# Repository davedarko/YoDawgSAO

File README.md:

# Yo Dawg, I heard you like add-ons on your badges?
With the hackaday supercon add-on contest in 2024, 
there came a lot of self-inflicted pressure of doing something great with the I2C pins and slap something smart on the PCBs. 
This sounded great, but what if you just want to do a small meme or have some RGB LEDs blinking?
What if you feel like that is not worthy of being a simple add-on made for the contest?

## design choices
To be safe with distance between badges, I decided on having the size constrained to 19mm x 19mm and using a 1.27mm pin header to connect GND-VCC-GND to the simple add-on mainboard. 
This header size was the wrong decision as it is a pain to solder - but it's the standard now!

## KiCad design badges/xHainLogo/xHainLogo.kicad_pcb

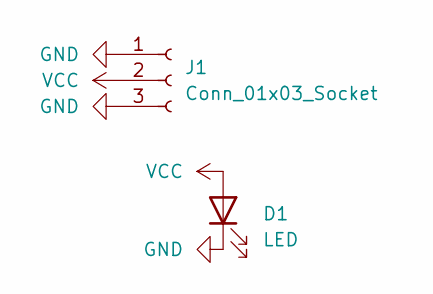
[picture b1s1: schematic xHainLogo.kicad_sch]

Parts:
D1: LED; LED_1210_3225Metric_Pad1.42x2.65mm_HandSolder
J1: Conn_01x03_Socket; PinHeader_1x03_P1.27mm_Vertical

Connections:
GND: D1.1 (K), J1.1, J1.3
VCC: D1.2 (A), J1.2

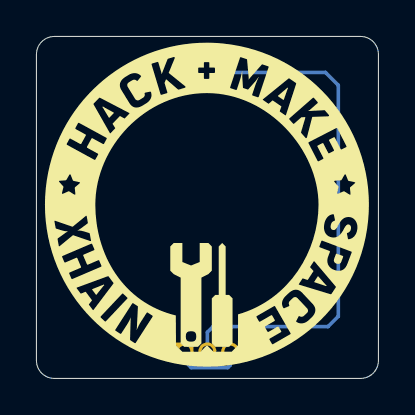
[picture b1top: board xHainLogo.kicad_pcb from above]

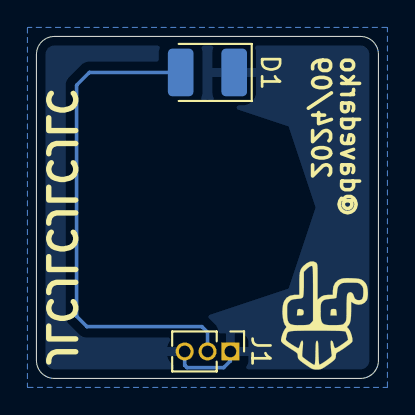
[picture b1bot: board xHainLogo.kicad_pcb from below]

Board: 2 copper layers, 19.0 x 19.0 mm, 3 parts (3 on the bottom side), 2 nets.

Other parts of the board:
Ref**: Val**; davedarko_logo_silk_outline

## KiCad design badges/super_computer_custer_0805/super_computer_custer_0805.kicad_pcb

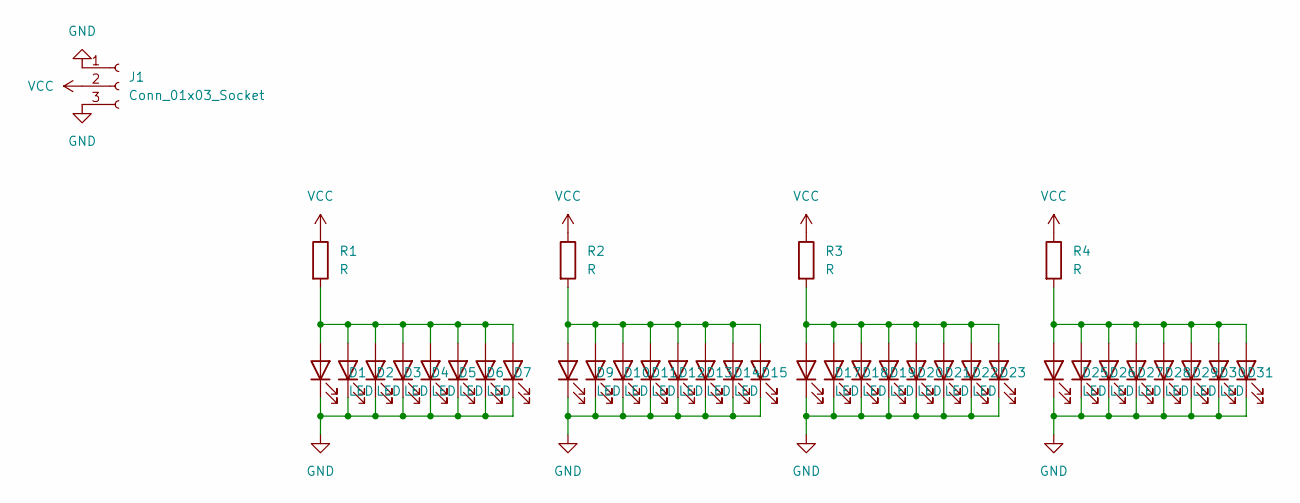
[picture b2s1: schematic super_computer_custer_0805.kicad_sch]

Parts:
D1, D2, D3, D4, D5, D6, D7, D8, D9, D10, D11, D12, D13, D14, D15, D16, D17, D18, D19, D20, D21, D22, D23, D24, D25, D26, D27, D28, D29, D30, D31, D32: LED; LED_0805_2012Metric_Pad1.15x1.40mm_HandSolder
J1: Conn_01x03_Socket; PinHeader_1x03_P1.27mm_Vertical
R1, R2, R3, R4: R; R_0603_1608Metric_Pad0.98x0.95mm_HandSolder

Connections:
GND: D1.1 (K), D2.1 (K), D3.1 (K), D4.1 (K), D5.1 (K), D6.1 (K), D7.1 (K), D8.1 (K), D9.1 (K), D10.1 (K), D11.1 (K), D12.1 (K), D13.1 (K), D14.1 (K), D15.1 (K), D16.1 (K), D17.1 (K), D18.1 (K), D19.1 (K), D20.1 (K), D21.1 (K), D22.1 (K), D23.1 (K), D24.1 (K), D25.1 (K), D26.1 (K), D27.1 (K), D28.1 (K), D29.1 (K), D30.1 (K), D31.1 (K), D32.1 (K), J1.1, J1.3
unnamed: D1.2 (A), D2.2 (A), D3.2 (A), D4.2 (A), D5.2 (A), D6.2 (A), D7.2 (A), D8.2 (A), R1.2
unnamed: D9.2 (A), D10.2 (A), D11.2 (A), D12.2 (A), D13.2 (A), D14.2 (A), D15.2 (A), D16.2 (A), R2.2
unnamed: D17.2 (A), D18.2 (A), D19.2 (A), D20.2 (A), D21.2 (A), D22.2 (A), D23.2 (A), D24.2 (A), R3.2
unnamed: D25.2 (A), D26.2 (A), D27.2 (A), D28.2 (A), D29.2 (A), D30.2 (A), D31.2 (A), D32.2 (A), R4.2
VCC: J1.2, R1.1, R2.1, R3.1, R4.1

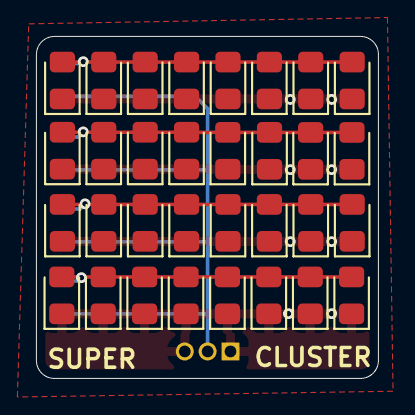
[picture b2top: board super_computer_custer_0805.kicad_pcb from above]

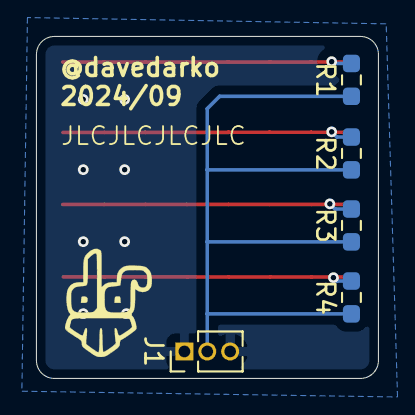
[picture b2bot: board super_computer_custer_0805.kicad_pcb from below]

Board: 2 copper layers, 19.0 x 19.0 mm, 38 parts (6 on the bottom side), 6 nets.

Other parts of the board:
Ref**: Val**; davedarko_logo_silk_outline

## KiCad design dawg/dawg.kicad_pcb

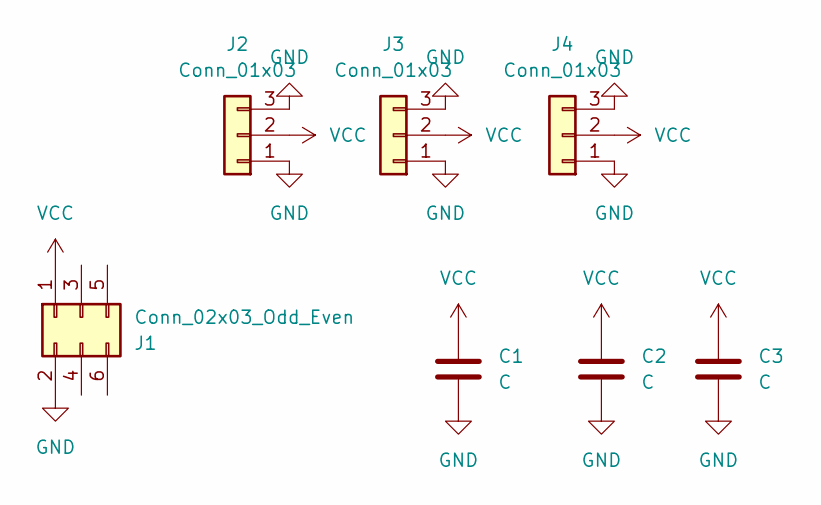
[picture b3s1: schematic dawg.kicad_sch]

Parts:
C1, C2, C3: C; C_0805_2012Metric_Pad1.18x1.45mm_HandSolder
J1: Conn_02x03_Odd_Even; IDC-Header_2x03_P2.54mm_Vertical
J2, J3, J4: Conn_01x03; PinSocket_1x03_P1.27mm_Vertical

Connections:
GND: C1.2, C2.2, C3.2, J1.2, J2.1, J2.3, J3.1, J3.3, J4.1, J4.3
VCC: C1.1, C2.1, C3.1, J1.1, J2.2, J3.2, J4.2

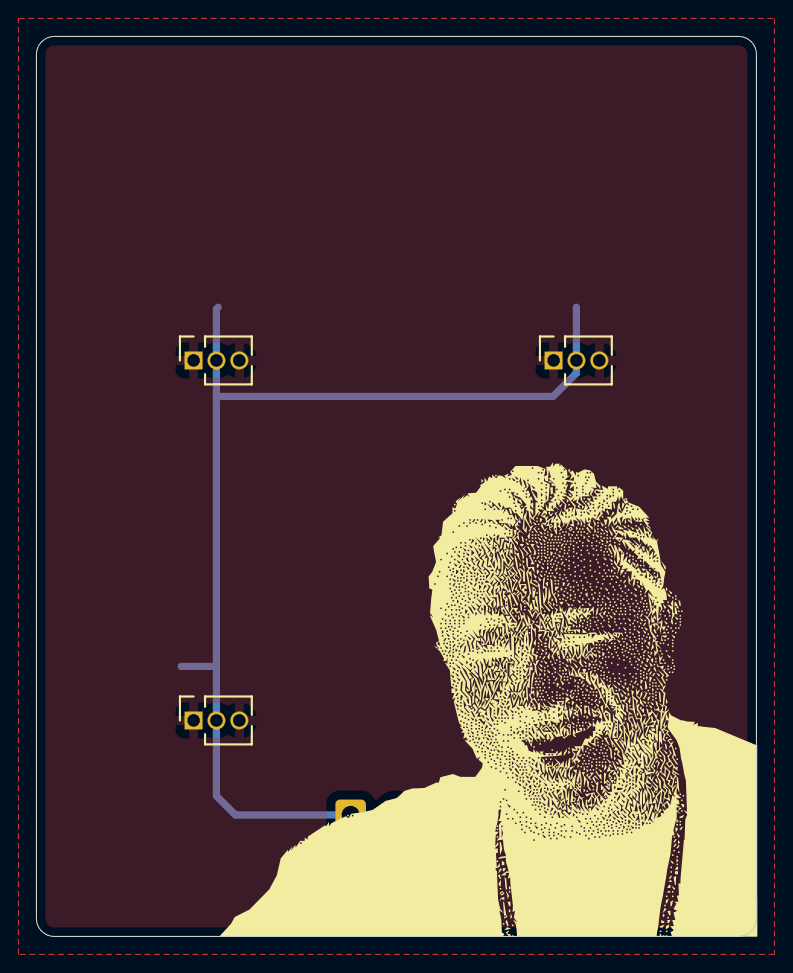
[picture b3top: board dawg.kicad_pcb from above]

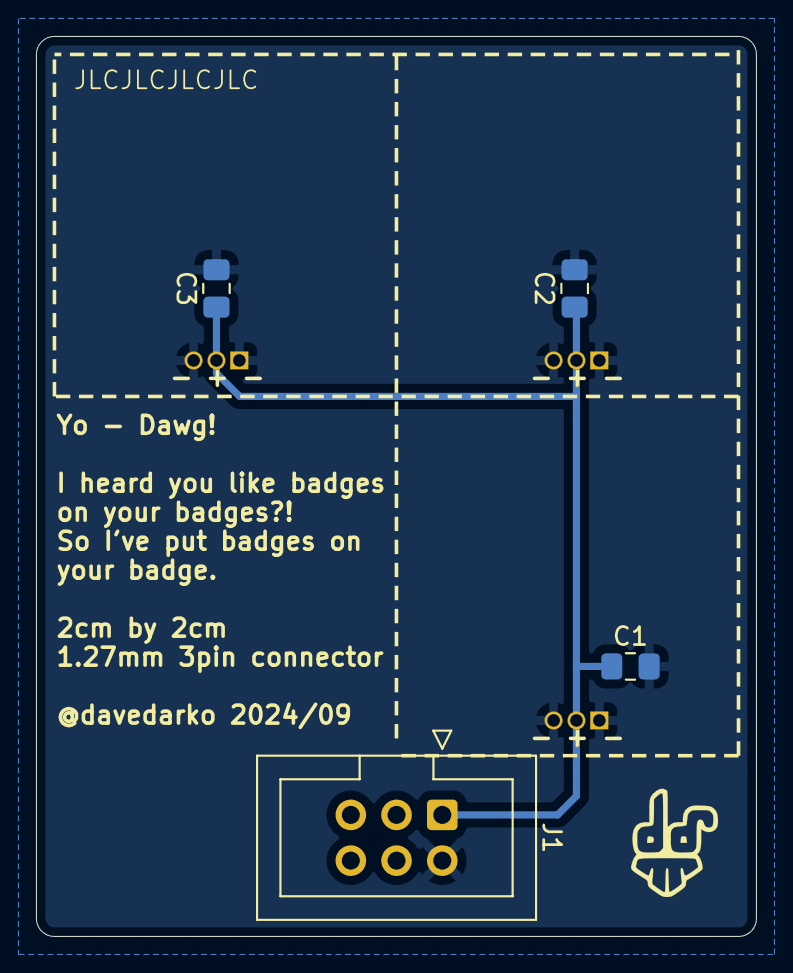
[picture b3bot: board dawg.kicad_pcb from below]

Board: 2 copper layers, 40.0 x 50.0 mm, 8 parts (5 on the bottom side), 2 nets.

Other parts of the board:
Ref**: Val**; davedarko_logo_silk_outline

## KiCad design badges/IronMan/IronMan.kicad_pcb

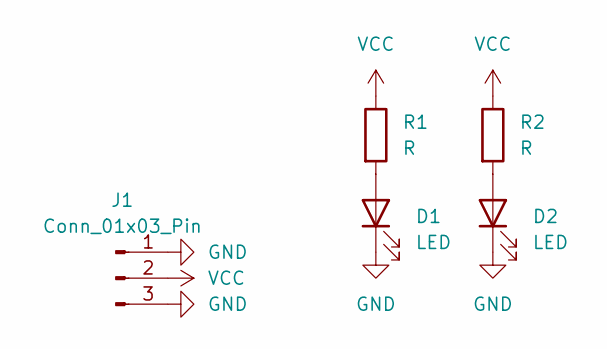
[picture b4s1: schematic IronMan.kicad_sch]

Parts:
D1, D2: LED; LED_1206_3216Metric_Pad1.42x1.75mm_HandSolder
J1: Conn_01x03_Pin; PinHeader_1x03_P1.27mm_Vertical
R1, R2: R; R_0603_1608Metric_Pad0.98x0.95mm_HandSolder

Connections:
GND: D1.1 (K), D2.1 (K), J1.1, J1.3
unnamed: D1.2 (A), R1.2
unnamed: D2.2 (A), R2.2
VCC: J1.2, R1.1, R2.1

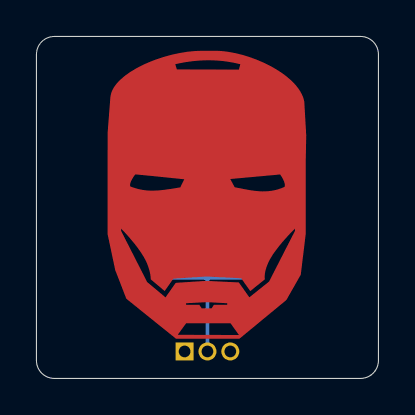
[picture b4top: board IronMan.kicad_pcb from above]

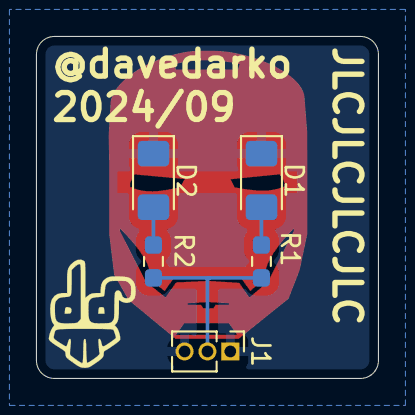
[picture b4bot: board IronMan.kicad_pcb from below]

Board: 2 copper layers, 19.0 x 19.0 mm, 6 parts (6 on the bottom side), 4 nets.

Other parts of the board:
Ref**: Val**; davedarko_logo_silk_outline

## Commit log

2024-10-11 SAOAO
